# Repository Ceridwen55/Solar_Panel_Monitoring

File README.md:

**Solar Panel Monitoring Demo (Arduino UNO + INA219 + DS3231 + microSD + I2C LCD)**

This project is a simple solar panel monitoring system based on Arduino UNO, designed to measure voltage (V), current (A), power (W), and energy (Wh) in real time. Data is displayed on a 16×2 I2C LCD and logged into a microSD card in CSV format for later analysis (Excel, Python, etc.).

**📦 Features**

Real-time monitoring of:

Voltage (V)

Current (A)

Power (W)

Energy accumulation (Wh)

Accurate timestamp using DS3231 RTC

Automatic data logging to microSD (CSV)

Live display on I2C LCD 16×2

Data smoothing using Exponential Moving Average (EMA)

Safe SD card handling with periodic flush every 5 writes

**🛠️ Hardware Components**
Component	Function
Arduino UNO	Main MCU for reading sensors & storing data
INA219	Measures voltage & current from the solar panel
DS3231 RTC	Provides real-time clock timestamp
LCD 16×2 I2C (0x27/0x3F)	Displays live monitoring data
MicroSD module (SPI)	Saves CSV logs
Capacitors & resistors	Decoupling & pull-up/pull-down if needed

**🔌 Pin Connections**
I2C — Arduino UNO
Device	SDA	SCL	Address
LCD 16×2 I2C	A4	A5	0x27 (common)
INA219	A4	A5	0x40
DS3231	A4	A5	0x68
SPI — MicroSD
Signal	Pin
CS	10
MOSI	11
MISO	12
SCK	13

⚠️ Use a 3.3V-regulated microSD module to avoid damaging the SD card.

**🧪 How It Works**

INA219 reads voltage and current from the solar panel.

The Arduino computes:

Power (P = V × I)

Accumulated energy (Wh)

EMA smoothing is applied to stabilize noisy readings.

DS3231 RTC provides accurate timestamps.

Data is shown on the LCD.

Data is logged into a CSV file on the microSD card:

timestamp,voltage_V,current_A,power_W,energy_Wh
2025-11-20 13:25:18,12.50,0.32,4.00,0.0011

Logging is always appended, never overwrites existing data.

**📁 CSV Log Structure
**
Columns:

timestamp

voltage_V

current_A

power_W

energy_Wh

Example:

2025-11-20 14:02:33,12.487,0.113,1.407,0.0041
2025-11-20 14:02:34,12.489,0.115,1.436,0.0045

**▶️ How to Use**

Connect all components according to the wiring table.

Load the provided code into Arduino IDE.

Install required libraries:

Adafruit INA219

RTClib

LiquidCrystal_I2C

SD

Upload the sketch to Arduino UNO.

Insert a FAT32-formatted microSD card.

Power the system and observe live monitoring on LCD or Serial Monitor.

**📸 LCD Display Example**

Line 1:

V:12.5,I:0.12

Line 2:

P:1.5,E:0.004

It also periodically shows the current time:

14:32:11

**⚙️ Technical Notes**

EMA smoothing uses:

EMA = (1 - α)*old + α*new
α = 0.25

Energy (Wh) is computed from smoothed power (W).

CSV is flushed every 5 writes to extend SD card life.

If RTC lost power, it auto-syncs to compile-time.

**📝 License**

This project is free to use for learning, research, or personal applications.

**🤝 Contributions**

Feel free to open issues or pull requests for improvements, bug fixes, or new features due this project is only a learning tools for me. Thanks

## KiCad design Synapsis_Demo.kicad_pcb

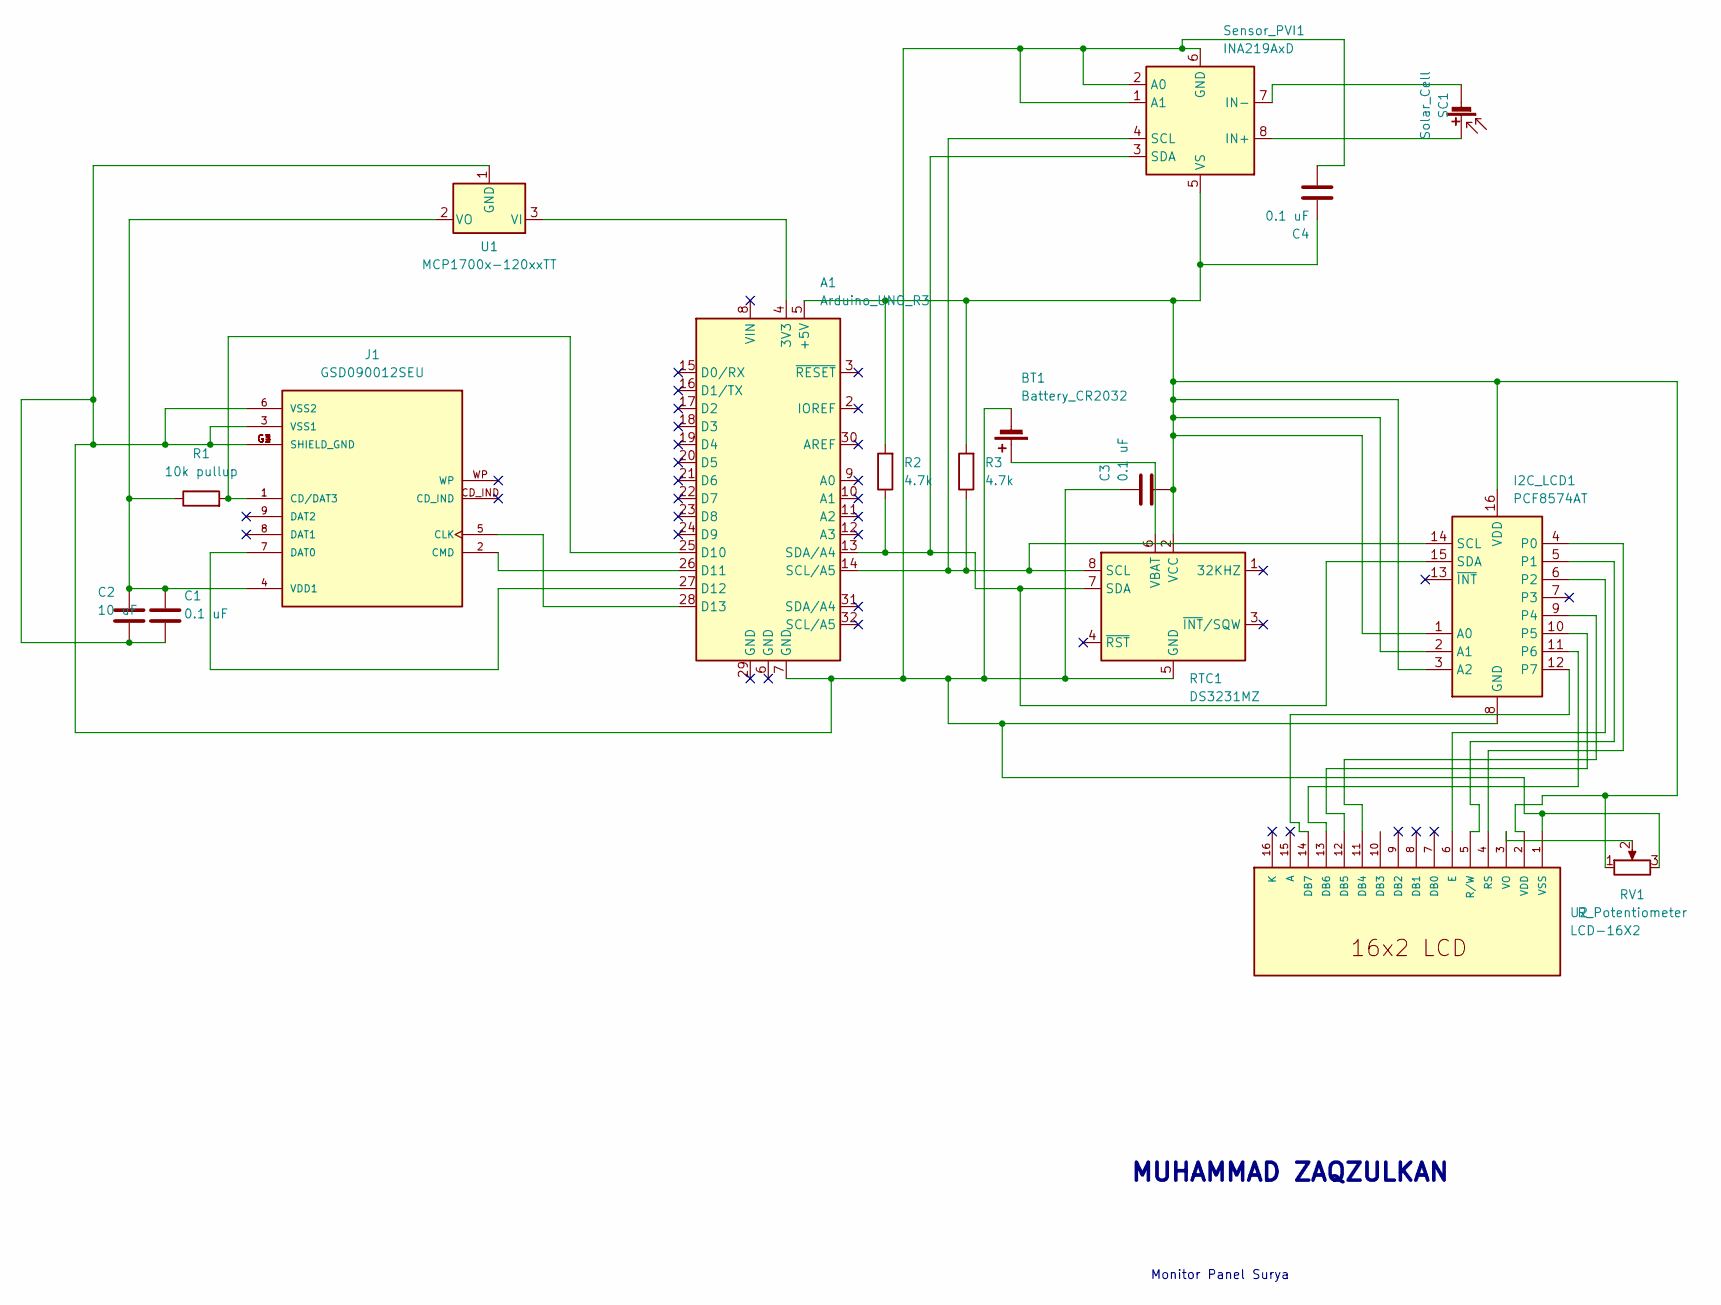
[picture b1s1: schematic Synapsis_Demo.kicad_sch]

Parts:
A1: Arduino_UNO_R3
BT1: Battery_CR2032; Battery_Panasonic_CR3032-VCN_Vertical_CircularHoles
C1, C3, C4: 0.1 uF; C_0603_1608Metric
C2: 10 uF; C_0603_1608Metric
I2C_LCD1: PCF8574AT; SOIC-16W_7.5x10.3mm_P1.27mm
J1: GSD090012SEU; AMPHENOL_GSD090012SEU; PARTREV E
R1: 10k pullup; R_0201_0603Metric
R2, R3: 4.7k; R_0201_0603Metric
RTC1: DS3231MZ; SOIC-8_3.9x4.9mm_P1.27mm
RV1: R_Potentiometer; Potentiometer_Bourns_3386P_Vertical
SC1: Solar_Cell; TerminalBlock_Phoenix_MKDS-1,5-2_1x02_P5.00mm_Horizontal
Sensor_PVI1: INA219AxD; SOIC-8_3.9x4.9mm_P1.27mm
U1: MCP1700x-120xxTT; SOT-23
U2: LCD-16X2; MODULE_LCD-16X2; PARTREV N/A

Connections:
unnamed: A1.4 (3V3), U1.3 (VI)
unnamed: A1.5 (+5V), C3.2, C4.1, I2C_LCD1.1 (A0), I2C_LCD1.2 (A1), I2C_LCD1.3 (A2), I2C_LCD1.16 (VDD), R2.2, R3.2, RTC1.2 (VCC), RV1.1, Sensor_PVI1.5 (VS), U2.2 (VDD)
unnamed: A1.25 (D10), J1.1 (CD/DAT3), R1.2
unnamed: A1.26 (D11), J1.2 (CMD)
unnamed: A1.27 (D12), J1.7 (DAT0)
unnamed: A1.28 (D13), J1.5 (CLK)
unnamed: BT1.1 (+), RTC1.6 (VBAT)
unnamed: A1.7 (GND), BT1.2 (-), C1.2, C2.2, C3.1, C4.2, I2C_LCD1.8 (GND), J1.3 (VSS1), J1.6 (VSS2), J1.G1 (SHIELD_GND), J1.G2 (SHIELD_GND), J1.G3 (SHIELD_GND), J1.G4 (SHIELD_GND), RTC1.5 (GND), RV1.3, Sensor_PVI1.1 (A1), Sensor_PVI1.2 (A0), Sensor_PVI1.6 (GND), U1.1 (GND), U2.1 (VSS)
unnamed: I2C_LCD1.4 (P0), U2.4 (RS)
unnamed: I2C_LCD1.5 (P1), U2.5 (R/W)
unnamed: I2C_LCD1.6 (P2), U2.6 (E)
unnamed: I2C_LCD1.9 (P4), U2.11 (DB4)
unnamed: I2C_LCD1.10 (P5), U2.12 (DB5)
unnamed: I2C_LCD1.11 (P6), U2.13 (DB6)
unnamed: I2C_LCD1.12 (P7), U2.14 (DB7)
unnamed: A1.14 (SCL/A5), I2C_LCD1.14 (SCL), R3.1, RTC1.8 (SCL), Sensor_PVI1.4 (SCL)
unnamed: A1.13 (SDA/A4), I2C_LCD1.15 (SDA), R2.1, RTC1.7 (SDA), Sensor_PVI1.3 (SDA)
unnamed: C1.1, C2.1, J1.4 (VDD1), R1.1, U1.2 (VO)
unnamed: SC1.1 (+), Sensor_PVI1.8 (IN+)
unnamed: SC1.2 (-), Sensor_PVI1.7 (IN-)
unnamed: RV1.2, U2.3 (VO)

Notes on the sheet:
MUHAMMAD ZAQZULKAN
Monitor Panel Surya

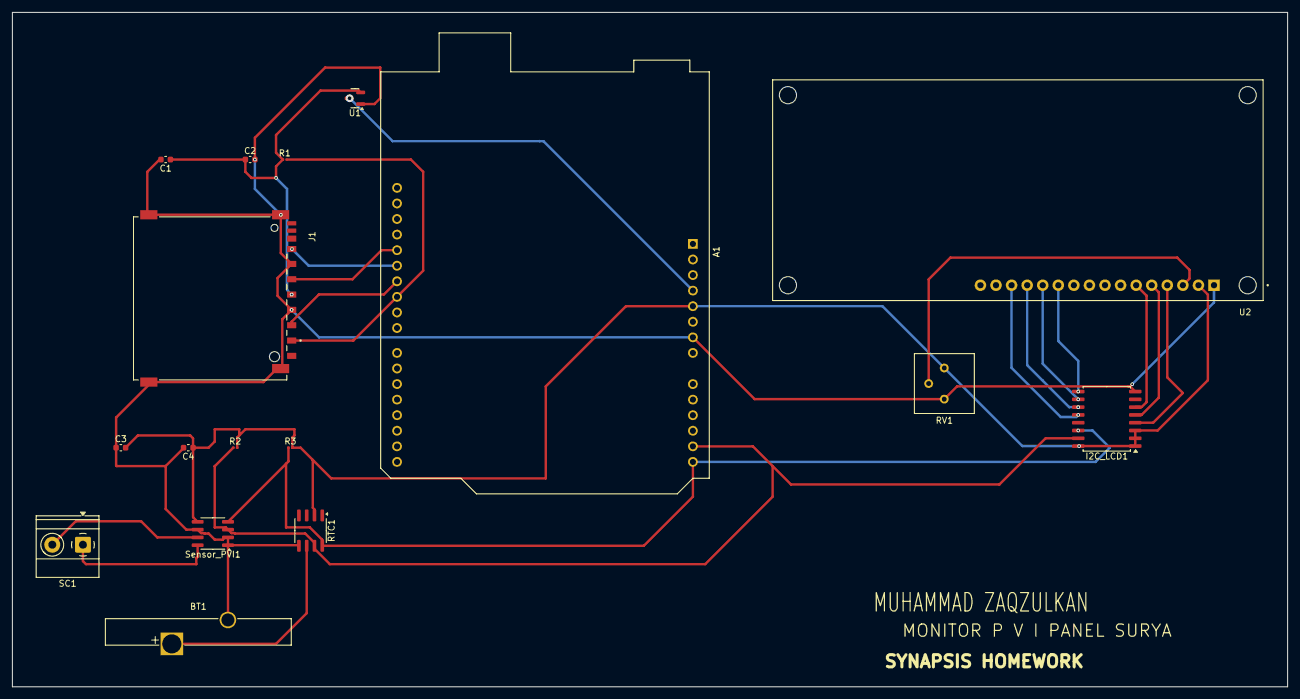
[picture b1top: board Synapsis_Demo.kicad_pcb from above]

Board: 2 copper layers, 208.0 x 110.0 mm, 17 parts (0 on the bottom side), 21 nets.

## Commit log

2025-11-19 Readme
    Explaining the project
2025-11-19 Second commit
